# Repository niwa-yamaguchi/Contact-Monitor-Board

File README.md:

# Contact Monitor Board

16 チャンネルの無電圧接点（ドライコンタクト）モニタ基板です。
リミットスイッチ・押しボタン・リレー接点などの ON/OFF を、単 4 電池 1 本だけで 16 点同時に LED 表示します。

装置の配線チェックや、盤内の接点動作確認を電源レスで行うための道具として設計しています。

- 基板サイズ: 100 × 100 mm / 2 層
- 電源: 単 4 電池 × 1（1.5 V）→ 昇圧 5 V
- 設計環境: KiCad 9

回路図は [Contact-Monitor-Board.pdf](Contact-Monitor-Board.pdf) でも閲覧できます（KiCad は不要です）。

## 外観

| 表面 | 裏面 |
| --- | --- |
|  |  |

表面は左上に電源部と観測用ヘッダ J17、下部に単 4 電池ホルダ（BT1）、右側に 2 列 × 8 の接点入力コネクタ（J1〜J16）を配置しています。各コネクタの脇に表示 LED があり、コネクタ番号と LED のリファレンスをシルク印字しています。写真は電源 ON の状態で、右上の電源表示 LED（D1）が点灯しています。中央の枠はチャンネル名を書き込めるラベル欄です。

裏面には回路図全体をシルクで印字しています。基板単体でも回路構成と J17 のピン配列を確認できます。

## 特徴

- **16 ch 一括表示** — 各チャンネルに 2 ピンコネクタと LED を 1 個ずつ。接点が閉じている ch の LED だけが点灯します。
- **電池 1 本で動作** — TPS61222 昇圧コンバータで単 4 電池 1 本から 5 V を生成。外部電源やアダプタは不要です。
- **ダイナミック点灯で低消費** — TLC555 + 74HC4017 でスキャンし、常時点灯するのは 16 ch 中 2 ch 分だけ。LED を全点灯させる方式に比べて平均電流を大きく下げています。
- **ch 間の回り込みなし** — 各チャンネルの帰り側に N-ch MOSFET を入れ、スキャンしていない ch を切り離しています。複数の接点が同時に閉じていても、他 ch を経由したゴースト点灯は起きません。
- **挿し間違えても偽陽性が出ない** — 本機のコネクタにハーネスをたすき掛けに挿してしまっても、LED と MOSFET を同じスキャン出力で駆動しているため点灯しません。接続ミスが「接点が閉じている」と誤表示されることがありません。
- **入手性重視の部品構成** — 全部品を JLCPCB / LCSC の在庫品で構成。抵抗は 470 Ω と 4.7 kΩ の 2 種類だけです。BOM・CPL・ガーバーを同梱しています。

## 動作原理

1 チャンネルの経路は次のとおりです。

```text
74HC4017 の出力 ──▶ LED ──▶ 470 Ω ──▶ Jn.1 ──[ 外部接点 ]──▶ Jn.2 ──▶ 2N7002(Qn) ──▶ GND
                                         （基板外の被測定接点）      ゲートは同じ出力で駆動
```

スキャン出力が H になると、その ch の LED 側と MOSFET 側が同時にアクティブになります。
外部接点が閉じていれば電流が流れて LED が点灯し、開いていれば経路が切れて消灯します。
出力が L の間はゲートも L なので MOSFET が OFF になり、その ch は完全に切り離されます。

スキャンの構成:

| ブロック | 内容 |
| --- | --- |
| クロック | TLC555 非安定発振（R18 4.7 k / R19 4.7 k / C3 100 nF、約 1 kHz） |
| スキャナ | 74HC4017 デコードカウンタ（Q9 を MR に接続した自己リセットで 9 ステップ） |
| ステップ割り当て | 8 ステップ × 2 ch = 16 ch、1 ステップは電源表示 LED（D1）。空きステップはありません |
| リフレッシュレート | 約 113 Hz（1 kHz ÷ 9 ステップ）— ちらつきは視認できません |

R20 は 4017 のクロック入力用プルアップとして基板パターン上に用意していますが、TLC555 の出力が CMOS プッシュプルのため不要です。**未実装（DNP）**とし、BOM・CPL からも除外しています。

LED 電流は各 ch の 470 Ω で制限しています。赤色 LED（Vf 2.0 V）で点灯時のピークが約 5 mA、デューティ 1/9 なので平均は約 0.6 mA です。
1 本の 4017 出力が 2 ch 分（LED 2 個 + MOSFET ゲート 2 個）を同時に駆動するため、ピーク時のピン電流は約 10 mA になります。
抵抗値をこれ以上下げる場合は、74HC4017 の出力電流（絶対最大定格 25 mA/ピン）が先に制約になる点に注意してください。

電源部は TPS61222（固定 5 V 出力）+ 4.7 µH インダクタの昇圧構成で、SW1（スライドスイッチ）が電池からの主電源スイッチです。

### 観測用ヘッダ J17

J17 はスキャン動作を確認するための 4 ピンヘッダ用ランドです（2.54 mm ピッチ）。基板上端、昇圧部（U3）と U2 の間にあり、各ピンの機能は基板表面にもシルク印字しています。1 番ピンは角ランドです。
R20 と同じく**未実装（DNP）**で、BOM・CPL からも除外しています。必要なときだけピンヘッダをはんだ付けして使ってください。

| ピン | シルク | 接続先 |
| --- | --- | --- |
| 1 | GND | GND |
| 2 | +5V | VCC（TPS61222 の 5 V 出力） |
| 3 | CLK | TLC555（U2）の出力 = 4017 のクロック入力 |
| 4 | RST | 4017 の Q9 出力 = MR（自己リセットのノード） |

CLK にオシロスコープを当てれば発振周波数を、RST を見ればスキャン 1 周（9 ステップ）の周期を確認できます。

> [!NOTE]
> CLK は U2 の出力に、RST は 4017 の Q9 出力に直結しています。どちらも CMOS プッシュプル出力なので、外部から信号を入力すると出力同士が衝突します。**観測専用の端子**として扱ってください。

## 接続間違い時の動作

本機の隣り合うコネクタで互い違いに接続しても、**その ch が点灯することはありません**。

各チャンネルは LED のアノードと MOSFET のゲートを**同じ 4017 出力**に接続しています。そのため電流が流れるのは、行き側（LED を通る経路）と帰り側（MOSFET を通る経路）が**同一ステップに属している場合だけ**です。

例として J1.1 を誤って J2.2 に接続した場合、次のようになります。

| タイミング | D2 のアノード | Q2 のゲート | 結果 |
| --- | --- | --- | --- |
| ステップ Q0（ch1） | H | L（Q2 は Q1 で駆動） | MOSFET が OFF、電流が流れない |
| ステップ Q1（ch2） | L（4017 が L に駆動） | H | アノードが GND 電位、電流が流れない |

どちらのタイミングでも点灯しないため、「閉じているはずの ch が点かない」という形で作業者が気づけます。

> [!NOTE]
> LED のアノードを VCC に直結する構成（部品点数を減らせる一般的な方式）にすると、ステップ Q1 のタイミングで D2 が点灯してしまい、正常な導通と区別がつかなくなります。アノードを 4017 出力に接続しているのはこのためで、意図的な設計です。

### 適用範囲

同一ステップを共有する 2 ch の間で入れ違えた場合だけは、原理上この保証が効きません。ペアは次のとおりです。

| 4017 出力 | 共有する ch |
| --- | --- |
| Q0 | ch1 / ch13 |
| Q1 | ch2 / ch14 |
| Q2 | ch3 / ch15 |
| Q3 | ch4 / ch16 |
| Q4 | 電源表示 D1（ch なし） |
| Q5 | ch5 / ch9 |
| Q6 | ch6 / ch10 |
| Q7 | ch7 / ch11 |
| Q8 | ch8 / ch12 |

コネクタは 2 列 × 8 の配置で、同一ステップのペアが基板上で約 43 mm 離れた対角位置になるよう割り当てています。

```text
   列 A（左）      列 B（右）
   J1  (Q0)       J9  (Q5)
   J2  (Q1)       J10 (Q6)
   J3  (Q2)       J11 (Q7)
   J4  (Q3)       J12 (Q8)
   J5  (Q5)       J13 (Q0)
   J6  (Q6)       J14 (Q1)
   J7  (Q7)       J15 (Q2)
   J8  (Q8)       J16 (Q3)
```

**物理的に隣接するコネクタの組み合わせは、縦・横・斜めのいずれもすべて異なるステップに属します。** したがって隣接コネクタへの挿し間違いは、全パターンが安全側に倒れます。

なお、これは「挿し間違いがあると点灯しない」という動作であり、接点が開いている場合・断線している場合と表示上は区別できません。いずれも点灯しない ch を調査すればよいため実用上の問題はありませんが、**挿し間違いが「導通あり」として点灯することはない**（偽陽性が出ない）というのが、この構成の保証する性質です。

## チャンネルと部品の対応

チャンネル *n* は次の組で構成されます（*n* = 1〜16）。

| 要素 | リファレンス |
| --- | --- |
| 接点入力コネクタ | J*n* |
| 表示 LED | D*(n+1)* |
| 電流制限抵抗 470 Ω | R*(n+1)* |
| スイッチング MOSFET | Q*n* |

D1 / R1 は電源表示用で、チャンネルには対応しません。

## 主要部品

| Ref | 部品 | 役割 | LCSC |
| --- | --- | --- | --- |
| U1 | 74HC4017D (SO-16) | デコードカウンタ（スキャナ） | C148206 |
| U2 | TLC555CD (SOIC-8) | スキャンクロック発振 | C6986 |
| U3 | TPS61222DCK (SC-70-6) | 昇圧 DC/DC（5 V 固定） | C116461 |
| L1 | 4.7 µH (1008) | 昇圧用インダクタ | C1329772 |
| Q1–Q16 | 2N7002 (SOT-23) | ch 切り離し用 N-ch MOSFET | C8545 |
| D2–D17 | LED (0603) | チャンネル表示 | C2286 |
| D1 | LED (0603) | 電源表示 | C2290 |
| R1–R17 | 470 Ω (0603) | LED 電流制限（R1 は電源表示用） | C23179 |
| R18, R19 | 4.7 kΩ (0603) | TLC555 発振用（R18 = Ra / R19 = Rb） | C23162 |
| J1–J16 | JST VH 相当 2 ピン（3.96 mm ピッチ・垂直） | 接点入力 | C160315 |
| SW1 | スライドスイッチ | 電源 ON/OFF | C5274456 |
| BT1 | BH-AAA-A1AJ001 | 単 4 電池ホルダ × 1 | C5290189 |

全リストは [jlcpcb/production_files/BOM-Contact-Monitor-Board.csv](jlcpcb/production_files/BOM-Contact-Monitor-Board.csv) を参照してください。

## 使い方

> [!WARNING]
> 電池は極性を確認してから入れてください。
> 本機に**逆接保護回路はありません**。
> 逆向きのまま SW1 を ON にすると、U3（TPS61222）の入力端子と L1 を通る経路で電池がほぼ短絡状態になり、電池の発熱と U3 の破損につながります。
> 電池の交換は SW1 を OFF にして行ってください。
> SW1 は電池の＋側直後にあるため、OFF であれば逆向きに入れても電流は流れません。

1. BT1 に単 4 電池を 1 本入れます。
2. SW1 を ON にすると、電源表示 LED（D1）が点灯します。
3. 調べたい接点を J1〜J16 のいずれかに接続します（極性はありません）。
4. 接点が閉じている ch の LED が点灯します。

> [!NOTE]
> 接点は**無電圧接点（ドライコンタクト）専用**です。
> 外部から電圧が加わっている端子には接続しないでください。

## ファイル構成

| パス | 内容 |
| --- | --- |
| `Contact-Monitor-Board.kicad_pro` | KiCad プロジェクトファイル |
| `Contact-Monitor-Board.kicad_sch` | 回路図 |
| `Contact-Monitor-Board.kicad_pcb` | 基板レイアウト |
| [Contact-Monitor-Board.pdf](Contact-Monitor-Board.pdf) | 回路図 PDF（KiCad 不要で閲覧可能） |
| [Library.pretty/](Library.pretty/) | プロジェクト固有フットプリント（電池ホルダ） |
| [jlcpcb/production_files/](jlcpcb/production_files/) | 製造用データ（ガーバー zip / BOM / CPL） |

## 製造

JLCPCB での発注を想定しています。

- 基板: 100 × 100 mm、2 層、標準厚 1.6 mm
- ガーバー: `jlcpcb/production_files/GERBER-Contact-Monitor-Board.zip`
- 実装（PCBA）を依頼する場合は、同ディレクトリの BOM / CPL をそのままアップロードできます。

## ライセンス

本プロジェクトのハードウェア設計（回路図・基板データ・フットプリント・製造データ）は
**CERN Open Hardware Licence Version 2 – Permissive (CERN-OHL-P v2)** で公開しています。

- SPDX 識別子: `CERN-OHL-P-2.0`
- ライセンス全文: [LICENSE](LICENSE)（原文: <https://ohwr.org/cern_ohl_p_v2.txt>）

このライセンスは、**いかなる保証もない**という条件のもとで、複製・改変・再頒布・商用利用を許諾するものです。
利用は自己責任でお願いします。

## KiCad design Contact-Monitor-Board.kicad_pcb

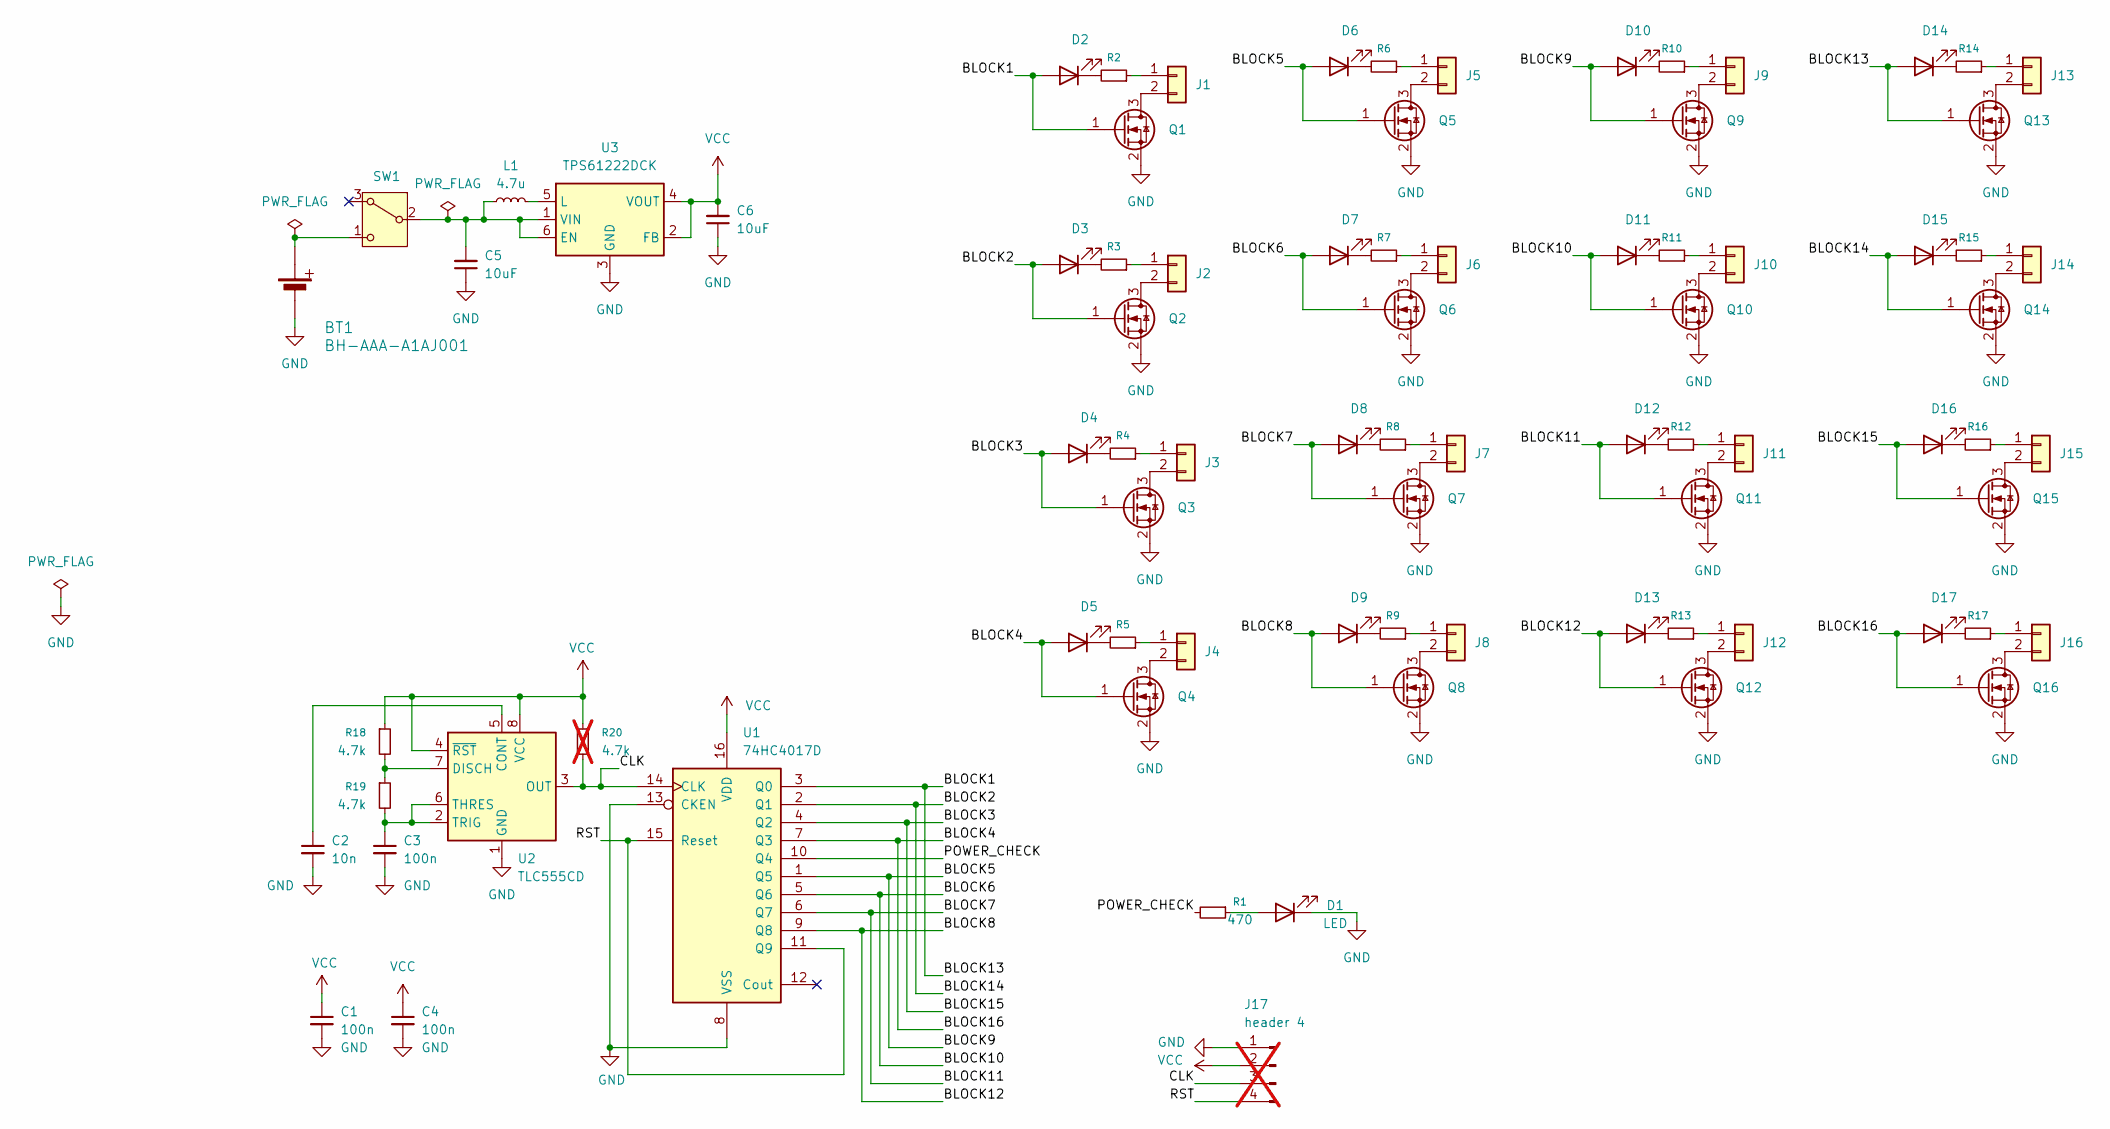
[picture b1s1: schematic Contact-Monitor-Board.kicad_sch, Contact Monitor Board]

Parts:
BT1: BH-AAA-A1AJ001
C1, C3, C4: 100n; C_0603_1608Metric
C2: 10n; C_0603_1608Metric
C5, C6: 10uF; C_0805_2012Metric
D1, D2, D3, D4, D5, D6, D7, D8, D9, D10, D11, D12, D13, D14, D15, D16, D17: LED; LED_0603_1608Metric
J1, J2, J3, J4, J5, J6, J7, J8, J9, J10, J11, J12, J13, J14, J15, J16: JST VH 02; JST_VH_B2P-VH_1x02_P3.96mm_Vertical
J17: header 4; PinHeader_1x04_P2.54mm_Vertical; not fitted
L1: 4.7u; L_1008_2520Metric
Q1, Q2, Q3, Q4, Q5, Q6, Q7, Q8, Q9, Q10, Q11, Q12, Q13, Q14, Q15, Q16: 2N7002; SOT-23
R1, R2, R3, R4, R5, R6, R7, R8, R9, R10, R11, R12, R13, R14, R15, R16, R17: 470; R_0603_1608Metric
R18, R19: 4.7k; R_0603_1608Metric
R20: 4.7k; R_0603_1608Metric; not fitted
SW1: KH-SS12D01-G3-5.0; SW_Slide-03_Wuerth-WS-SLTV_10x2.5x6.4_P2.54mm
U1: 74HC4017D; SO-16_3.9x9.9mm_P1.27mm
U2: TLC555CD; SOIC-8_3.9x4.9mm_P1.27mm
U3: TPS61222DCK; Texas_R-PDSO-G6

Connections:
/BLOCK1: D2.2 (A), D14.2 (A), Q1.1 (G), Q13.1 (G), U1.3 (Q0)
/BLOCK5: D6.2 (A), D10.2 (A), Q5.1 (G), Q9.1 (G), U1.1 (Q5)
/BLOCK10: D7.2 (A), D11.2 (A), Q6.1 (G), Q10.1 (G), U1.5 (Q6)
/BLOCK11: D8.2 (A), D12.2 (A), Q7.1 (G), Q11.1 (G), U1.6 (Q7)
/BLOCK12: D9.2 (A), D13.2 (A), Q8.1 (G), Q12.1 (G), U1.9 (Q8)
/BLOCK14: D3.2 (A), D15.2 (A), Q2.1 (G), Q14.1 (G), U1.2 (Q1)
/BLOCK15: D4.2 (A), D16.2 (A), Q3.1 (G), Q15.1 (G), U1.4 (Q2)
/BLOCK16: D5.2 (A), D17.2 (A), Q4.1 (G), Q16.1 (G), U1.7 (Q3)
/CLK: J17.3, R20.2, U1.14 (CLK), U2.3 (OUT)
/POWER_CHECK: R1.2, U1.10 (Q4)
/RST: J17.4, U1.11 (Q9), U1.15 (Reset)
GND: BT1.2 (MINUS), C1.2, C2.2, C3.2, C4.2, C5.1, C6.1, D1.1 (K), J17.1, Q1.2 (S), Q2.2 (S), Q3.2 (S), Q4.2 (S), Q5.2 (S), Q6.2 (S), Q7.2 (S), Q8.2 (S), Q9.2 (S), Q10.2 (S), Q11.2 (S), Q12.2 (S), Q13.2 (S), Q14.2 (S), Q15.2 (S), Q16.2 (S), U1.8 (VSS), U1.13 (CKEN), U2.1 (GND), U3.3 (GND)
unnamed: BT1.1 (PLUS), SW1.1 (C)
unnamed: D1.2 (A), R1.1
unnamed: D2.1 (K), R2.2
unnamed: D3.1 (K), R3.2
unnamed: D4.1 (K), R4.2
unnamed: D5.1 (K), R5.2
unnamed: D6.1 (K), R6.2
unnamed: D7.1 (K), R7.2
unnamed: D8.1 (K), R8.2
unnamed: D9.1 (K), R9.2
unnamed: D10.1 (K), R10.2
unnamed: D11.1 (K), R11.2
unnamed: D12.1 (K), R12.2
unnamed: D13.1 (K), R13.2
unnamed: D14.1 (K), R14.2
unnamed: D15.1 (K), R15.2
unnamed: D16.1 (K), R16.2
unnamed: D17.1 (K), R17.2
unnamed: J1.1, R2.1
unnamed: J1.2, Q1.3 (D)
unnamed: J2.1, R3.1
unnamed: J2.2, Q2.3 (D)
unnamed: J3.1, R4.1
unnamed: J3.2, Q3.3 (D)
unnamed: J4.1, R5.1
unnamed: J4.2, Q4.3 (D)
unnamed: J5.1, R6.1
unnamed: J5.2, Q5.3 (D)
unnamed: J6.1, R7.1
unnamed: J6.2, Q6.3 (D)
unnamed: J7.1, R8.1
unnamed: J7.2, Q7.3 (D)
unnamed: J8.1, R9.1
unnamed: J8.2, Q8.3 (D)
unnamed: J9.1, R10.1
unnamed: J9.2, Q9.3 (D)
unnamed: J10.1, R11.1
unnamed: J10.2, Q10.3 (D)
unnamed: J11.1, R12.1
unnamed: J11.2, Q11.3 (D)
unnamed: J12.1, R13.1
unnamed: J12.2, Q12.3 (D)
unnamed: J13.1, R14.1
unnamed: J13.2, Q13.3 (D)
unnamed: J14.1, R15.1
unnamed: J14.2, Q14.3 (D)
unnamed: J15.1, R16.1
unnamed: J15.2, Q15.3 (D)
unnamed: J16.1, R17.1
unnamed: J16.2, Q16.3 (D)
unnamed: C5.2, L1.1, SW1.2 (B), U3.1 (VIN), U3.6 (EN)
unnamed: C2.1, U2.5 (CONT)
unnamed: R18.2, R19.1, U2.7 (DISCH)
unnamed: C3.1, R19.2, U2.2 (TRIG), U2.6 (THRES)
unnamed: L1.2, U3.5 (L)
VCC: C1.1, C4.1, C6.2, J17.2, R18.1, R20.1, U1.16 (VDD), U2.4 (~RST), U2.8 (VCC), U3.2 (FB), U3.4 (VOUT)

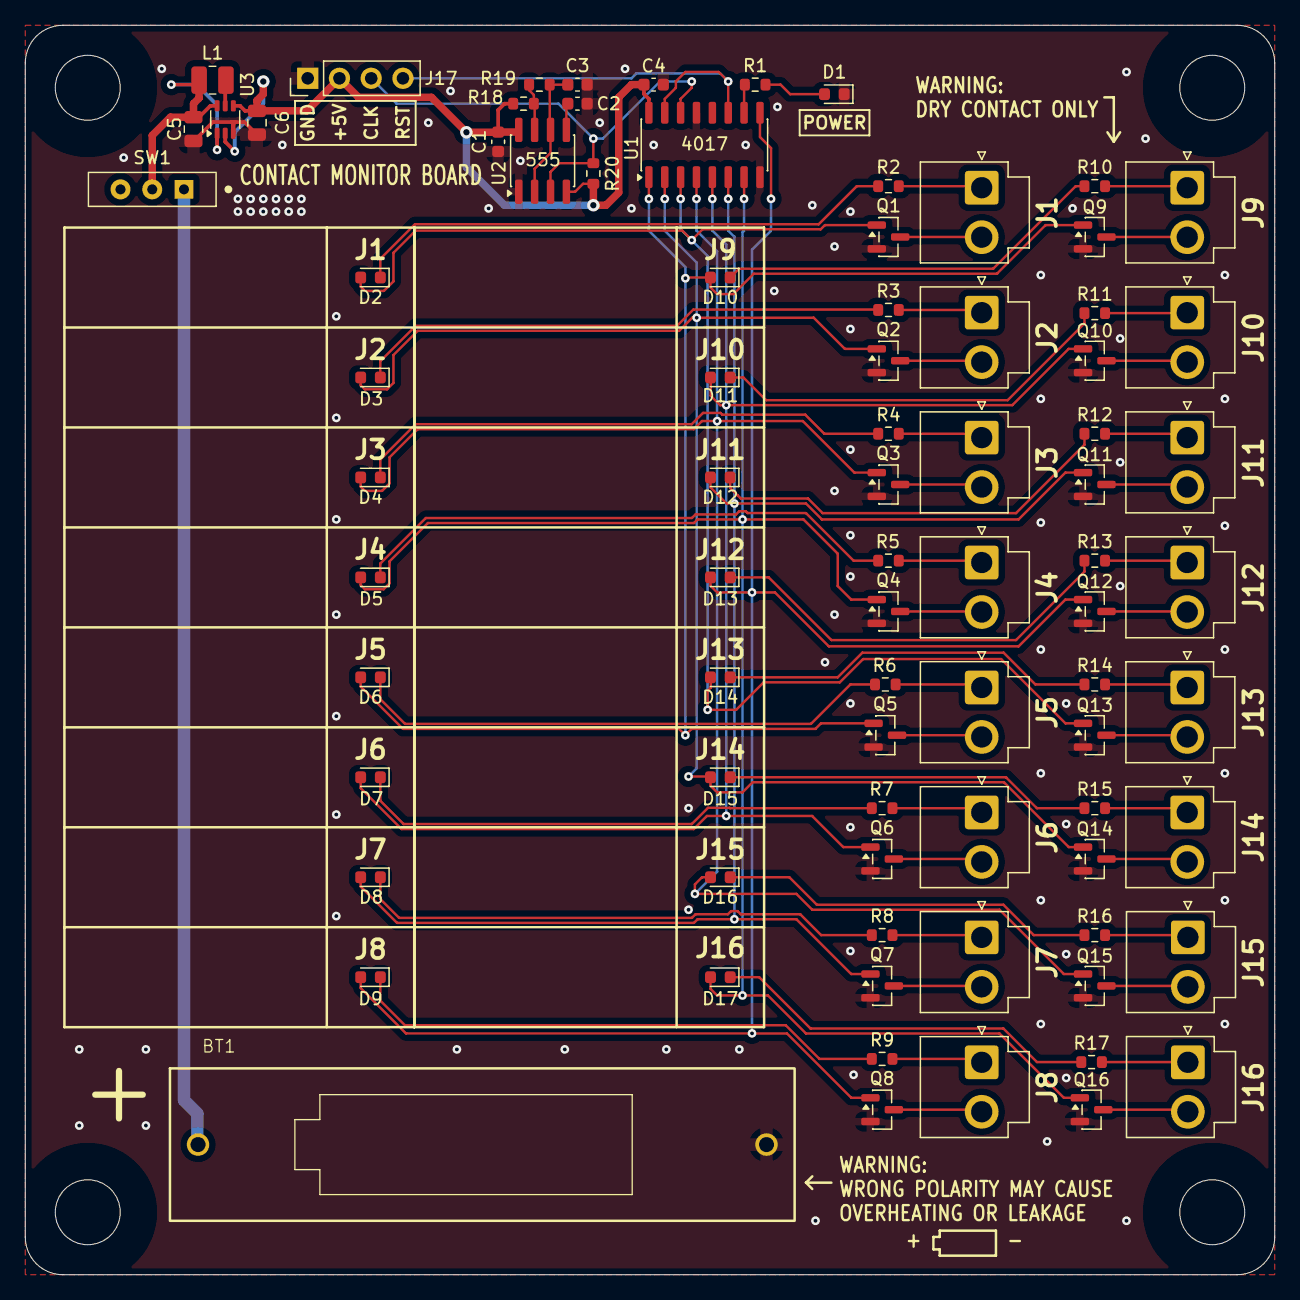
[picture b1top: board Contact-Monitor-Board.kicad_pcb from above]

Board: 2 copper layers, 100.0 x 100.0 mm, 83 parts (1 on the bottom side), 68 nets.

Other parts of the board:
QR*****: URL

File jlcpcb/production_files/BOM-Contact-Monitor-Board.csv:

Comment,Designator,Footprint,LCSC,Quantity
100n,"C1,C3,C4",C_0603_1608Metric,C14663,3
10n,C2,C_0603_1608Metric,C57112,1
10uF,"C5,C6",C_0805_2012Metric,C440198,2
2N7002,"Q1,Q10,Q11,Q12,Q13,Q14,Q15,Q16,Q2,Q3,Q4,Q5,Q6,Q7,Q8,Q9",SOT-23,C8545,16
4.7k,"R18,R19",R_0603_1608Metric,C23162,2
4.7u,L1,L_1008_2520Metric,C1329772,1
470,"R1,R10,R11,R12,R13,R14,R15,R16,R17,R2,R3,R4,R5,R6,R7,R8,R9",R_0603_1608Metric,C23179,17
74HC4017D,U1,SO-16_3.9x9.9mm_P1.27mm,C148206,1
BH-AAA-A1AJ001,BT1,BH-AAA-A1AJ001,C5290189,1
JST VH 02,"J1,J10,J11,J12,J13,J14,J15,J16,J2,J3,J4,J5,J6,J7,J8,J9",JST_VH_B2P-VH_1x02_P3.96mm_Vertical,C160315,16
KH-SS12D01-G3-5.0,SW1,SW_Slide-03_Wuerth-WS-SLTV_10x2.5x6.4_P2.54mm,C5274456,1
LED,"D10,D11,D12,D13,D14,D15,D16,D17,D2,D3,D4,D5,D6,D7,D8,D9",LED_0603_1608Metric,C2286,16
LED,D1,LED_0603_1608Metric,C2290,1
TLC555CD,U2,SOIC-8_3.9x4.9mm_P1.27mm,C6986,1
TPS61222DCK,U3,Texas_R-PDSO-G6,C116461,1

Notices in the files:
Contact-Monitor-Board.kicad_pcb:
Copyright (c) 2026 Satoru Yamaguchi
SPDX-License-Identifier: CERN-OHL-P-2.0
Licensed under CERN-OHL-P v2 - https://ohwr.org/cern_ohl_p_v2.txt
CERN-OHL-P v2
